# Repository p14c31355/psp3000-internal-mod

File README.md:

# psp3000-internal-mod
PSP-3000 internal SBC, display adapter, power, USB-C, PCB and mechanical integration project.

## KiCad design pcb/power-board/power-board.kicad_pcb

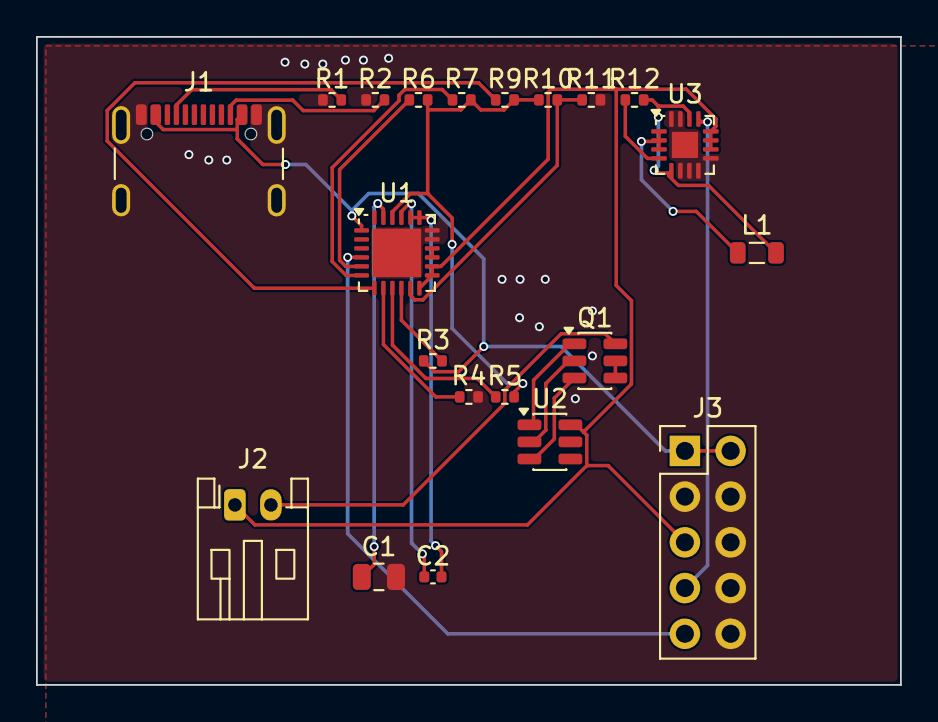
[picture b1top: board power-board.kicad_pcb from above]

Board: 2 copper layers, 48.0 x 36.0 mm, 21 parts (0 on the bottom side), 27 nets.

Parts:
C1: C_0805_2012Metric
C2: C_0402_1005Metric
J1: USB_C_Receptacle_GCT_USB4105-xx-A_16P_TopMnt_Hori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; USB_C_Receptacle_GCT_USB4105-xx-A_16P_TopMnt_Horizontal
J2: JST_PH_S2B-PH-K_1x02_P2.00mm_Horizontal
J3: PinHeader_2x05_P2.54mm_Vertical
L1: L_0805_2012Metric
Q1: SOT-23-6
R1, R2, R3, R4, R5, R6, R7, R9, R10, R11, R12: R_0402_1005Metric
U1: Texas_RTW_WQFN-24-1EP_4x4mm_P0.5mm_EP2.7x2.7mm
U2: SOT-23-6
U3: VQFN-16-1EP_3x3mm_P0.5mm_EP1.45x1.45mm

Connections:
/BAT: J2.1, J3.5, U1.12, U1.13, U1.14, U2.6, U3.10, U3.11, U3.12
/BATGND: Q1.2, U2.2
/BTST: C2.1, U1.21
/CC1: J1.A5, R1.2
/CC2: J1.B5, R2.2
/CE: R5.1, U1.9
/EN33: J3.7, U3.13
/FETMID: Q1.4, Q1.5
/ILIM: R3.2, U1.10
/INT: R9.1, U1.7
/OTG: R4.1, U1.8
/PACKNEG: J2.2, Q1.6
/PG33: R12.1, U3.4
/PMID: C1.1, U1.23
/PROT_OC: Q1.3, U2.3
/PROT_OD: Q1.1, U2.1
/REGN: R5.2, R6.2, R7.2, R9.2, R10.1, U1.22
/SCL: R6.1, U1.5
/SDA: R7.1, U1.6
/STAT: J3.9, U1.4
/SW: C2.2, U1.19, U1.20
/SW33: L1.1, U3.1, U3.2, U3.3
/SYS: U1.15, U1.16
/TS: R10.2, R11.1, U1.11
/VBUS: J1.A4, J1.A9, J1.B4, J1.B9, J3.1, J3.2, R3.1, U1.1
/VOS33: L1.2, R12.2, U3.5, U3.14
GND: C1.2, J1.A1, J1.A12, J1.B1, J1.B12, J1.SH, J3.3, J3.4, J3.6, J3.8, J3.10, R1.1, R2.1, R4.2, R11.2, U1.17, U1.18, U1.25, U3.6, U3.7, U3.8, U3.9, U3.15, U3.16, U3.17

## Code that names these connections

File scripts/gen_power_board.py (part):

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    u2c = 220.0
    q1c = 252.0
    j2c = 175.0
    # battery connector: pin1 = BAT+ (pack positive), pin2 = BAT- (pack neg)
    _pin_stub(j2, "1", "BAT", "j2", RIGHT)
    _pin_stub(j2, "2", "PACKNEG", "j2", RIGHT)
    # DW01A: VCC (pin? per DW01A SOT-23-6: 1=OD 2=CS 3=OC 4=TD 5=NC 6=VCC
    # per SparkFun DW01-P: 1 OD, 2 CS (current sense / GND), 3 OC, 4 TD
    # (test), 5 NC, 6 VCC. GND is pin 2 (CS is the GND/current sense).
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    # 10,11,12 VIN / 13 EN / 14 VOS. Same-potential pins share coordinates.
    u3c = 265.0
    u3_nets = {
        "1": "SW33", "2": "SW33", "3": "SW33", "4": "PG33",
        "5": "VOS33", "6": "GND", "7": "GND", "8": "GND",
        "9": "GND", "10": "BAT", "11": "BAT", "12": "BAT",
        "13": "EN33", "14": "VOS33", "15": "GND", "16": "GND",
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        "L1", "2.2uH", "Inductor_SMD:L_0805_2012Metric",
        295.0, 70.0, "Device", "L", "L1")
    _pin_stub(l1, "1", "SW33", "l1", _pin_side(l1, "1", 295.0))
    _pin_stub(l1, "2", "VOS33", "l1", _pin_side(l1, "2", 295.0))
    # R3 ILIM: VBUS -> ILIM (KILIM 390 typ, 2A -> 195 ohm -> E96 196R)
    r3 = SCHEMATIC.instance(
        "R3", "196R", "Resistor_SMD:R_0402_1005Metric",
        155.0, 40.0, "Device", "R", "R3")
    _pin_stub(r3, "1", "VBUS", "r3", _pin_side(r3, "1", 155.0))
    _pin_stub(r3, "2", "ILIM", "r3", _pin_side(r3, "2", 155.0))
    # R4 OTG pulldown: OTG -> GND (OTG disabled by default)
    r4 = SCHEMATIC.instance(
        "R4", "100k", "Resistor_SMD:R_0402_1005Metric",
        165.0, 40.0, "Device", "R", "R4")
    _pin_stub(r4, "1", "OTG", "r4", _pin_side(r4, "1", 165.0))
    _pin_stub(r4, "2", "GND", "r4", _pin_side(r4, "2", 165.0))
    # R5 CE pullup: CE -> REGN (charging enabled by default)
    r5 = SCHEMATIC.instance(
        "R5", "100k", "Resistor_SMD:R_0402_1005Metric",
        175.0, 40.0, "Device", "R", "R5")
    _pin_stub(r5, "1", "CE", "r5", _pin_side(r5, "1", 175.0))
    _pin_stub(r5, "2", "REGN", "r5", _pin_side(r5, "2", 175.0))
    # R6/R7/R9: I2C + INT pullups to REGN.  R8 (STAT) is intentionally
    # absent: STAT is open-drain and its pull-up lives on the Radxa side
    # (3.3 V) - see docs/harness-j3-radxa.md and UNKNOWNS U11.  Pulling
    # STAT to REGN (4.7 V) would over-stress the SBC GPIO.
    for ref, net, x in (("R6", "SCL", 165.0), ("R7", "SDA", 175.0),
                        ("R9", "INT", 195.0)):
        r = SCHEMATIC.instance(
            ref, "10k", "Resistor_SMD:R_0402_1005Metric",
            x, 30.0, "Device", "R", ref)
        _pin_stub(r, "1", net, ref.lower(), _pin_side(r, "1", x))
        _pin_stub(r, "2", "REGN", ref.lower(), _pin_side(r, "2", x))
    # C1 PMID bypass 8.2uF (datasheet no-OTG value), PMID -> GND
    c1 = SCHEMATIC.instance(
        "C1", "8.2uF", "Capacitor_SMD:C_0805_2012Metric",
        205.0, 40.0, "Device", "C", "C1")
    _pin_stub(c1, "1", "PMID", "c1", _pin_side(c1, "1", 205.0))
    _pin_stub(c1, "2", "GND", "c1", _pin_side(c1, "2", 205.0))
    # C2 bootstrap cap 0.047uF BTST -> SW (datasheet)
    c2 = SCHEMATIC.instance(
        "C2", "47nF", "Capacitor_SMD:C_0402_1005Metric",
        215.0, 40.0, "Device", "C", "C2")
    _pin_stub(c2, "1", "BTST", "c2", _pin_side(c2, "1", 215.0))
    _pin_stub(c2, "2", "SW", "c2", _pin_side(c2, "2", 215.0))
    # TS divider: R10 REGN->TS, R11 TS->GND (103AT-2 style mid-scale,
    # enables charging without an NTC for bench bring-up; the donor
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    r10 = SCHEMATIC.instance(
        "R10", "10k", "Resistor_SMD:R_0402_1005Metric",
        225.0, 40.0, "Device", "R", "R10")
    _pin_stub(r10, "1", "REGN", "r10", _pin_side(r10, "1", 225.0))
    _pin_stub(r10, "2", "TS", "r10", _pin_side(r10, "2", 225.0))
    r11 = SCHEMATIC.instance(
        "R11", "10k", "Resistor_SMD:R_0402_1005Metric",
        235.0, 40.0, "Device", "R", "R11")
    _pin_stub(r11, "1", "TS", "r11", _pin_side(r11, "1", 235.0))
    _pin_stub(r11, "2", "GND", "r11", _pin_side(r11, "2", 235.0))
    # R12 PG33 pullup to VOS33 (open-drain power-good)
    r12 = SCHEMATIC.instance(
        "R12", "10k", "Resistor_SMD:R_0402_1005Metric",
        245.0, 40.0, "Device", "R", "R12")
    _pin_stub(r12, "1", "PG33", "r12", _pin_side(r12, "1", 245.0))
    _pin_stub(r12, "2", "VOS33", "r12", _pin_side(r12, "2", 245.0))
    # power flags so ERC sees GND and BAT as driven sources
    SCHEMATIC.pwr_flag(139.7, 129.54, "GND", "gnd")
    SCHEMATIC.pwr_flag(149.86, 129.54, "BAT", "bat")
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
